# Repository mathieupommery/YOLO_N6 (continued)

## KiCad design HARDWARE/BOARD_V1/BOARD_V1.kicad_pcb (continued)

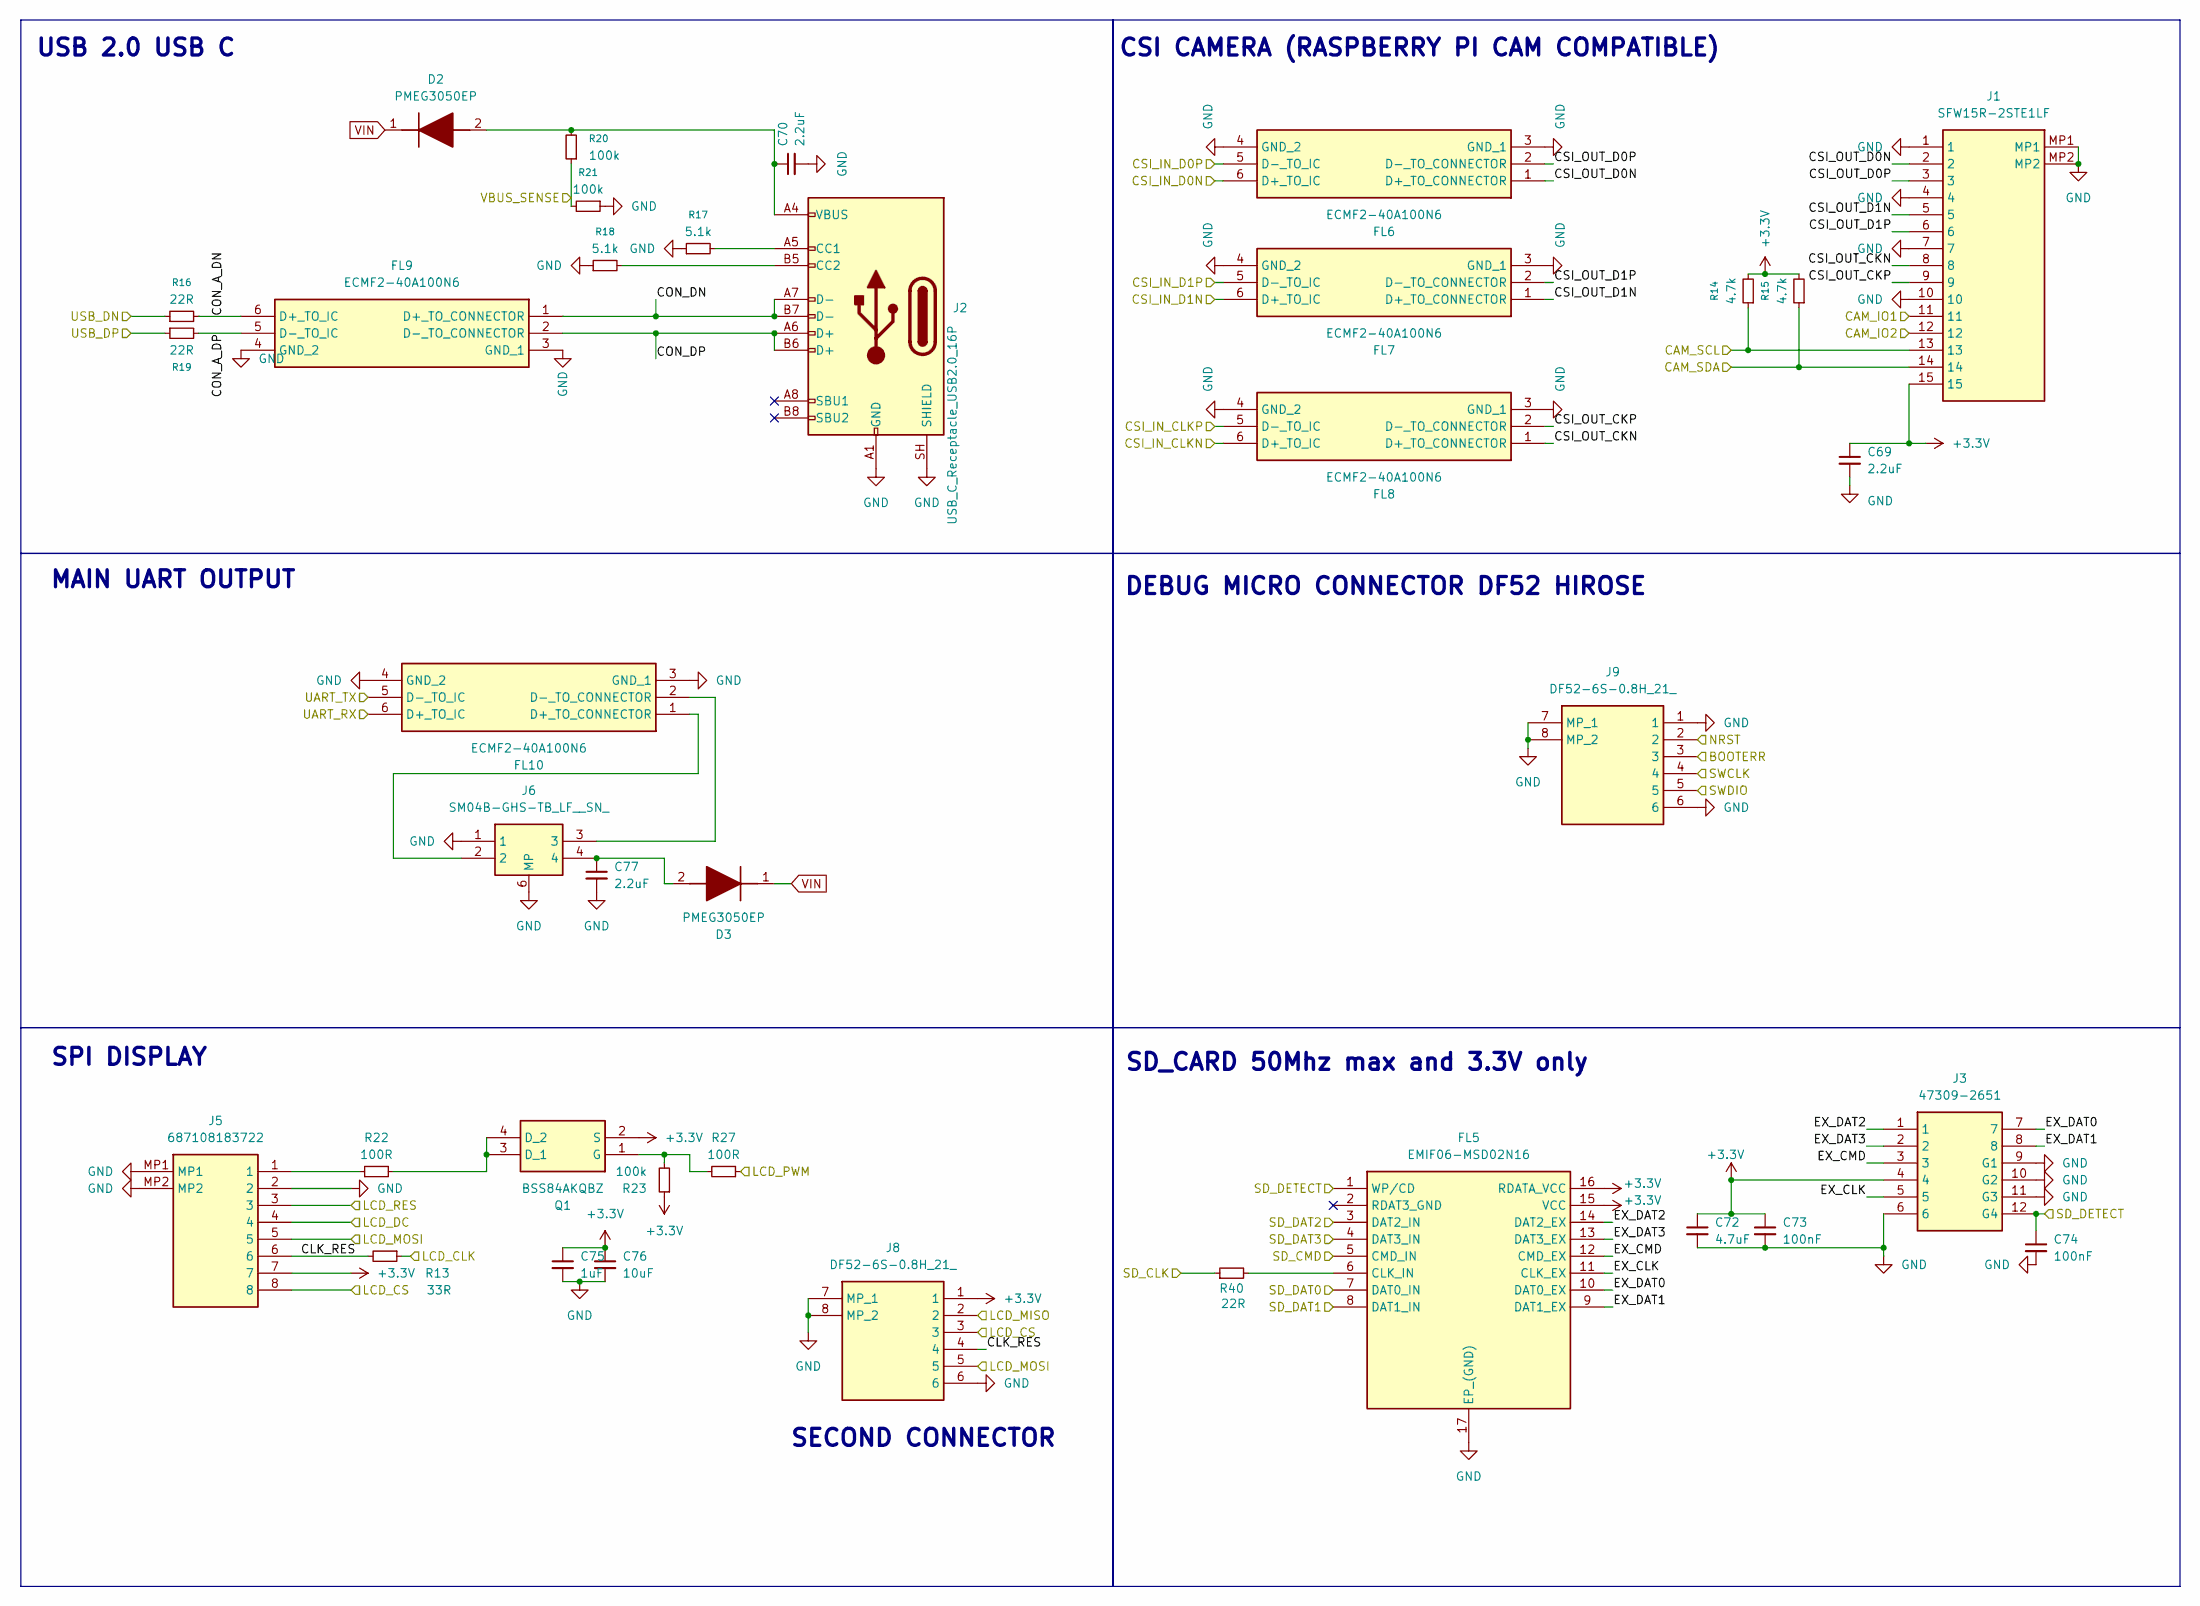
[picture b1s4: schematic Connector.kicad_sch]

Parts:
C69, C70, C77: 2.2uF; C_0402_1005Metric_Pad0.74x0.62mm_HandSolder
C72: 4.7uF; C_0402_1005Metric_Pad0.74x0.62mm_HandSolder
C73, C74: 100nF; C_0201_0603Metric_Pad0.64x0.40mm_HandSolder
C75: 1uF; C_0201_0603Metric_Pad0.64x0.40mm_HandSolder
C76: 10uF; C_0402_1005Metric_Pad0.74x0.62mm_HandSolder
D2, D3: PMEG3050EP; SOD4725X110N; Manufacturer_Part_Number PMEG3050EP; Mouser Part Number 771-PMEG3050EP115
FL5: EMIF06-MSD02N16; EMIF06MSD02N16; Manufacturer_Part_Number EMIF06-MSD02N16; Mouser Part Number 511-EMIF06-MSD02N16
FL6, FL7, FL8, FL9, FL10: ECMF2-40A100N6; ECMF240A100N6; Manufacturer_Part_Number ECMF2-40A100N6; Mouser Part Number 511-ECMF2-40A100N6
J1: SFW15R-2STE1LF; SFW15R2STE1LF; Manufacturer_Part_Number SFW15R-2STE1LF; Mouser Part Number 649-SFW15R-2STE1LF
J2: USB_C_Receptacle_USB2.0_16P; USB_C_Receptacle_GCT_USB4110; Mouser Part Number 640-USB4110-GF-A
J3: 47309-2651; 473092651; Manufacturer_Part_Number 47309-2651; Mouser Part Number 538-47309-2651
J5: 687108183722; Mouser Part Number 710-687108183722
J6: SM04B-GHS-TB_LF__SN_; SM04B-GHS-TB; Manufacturer_Part_Number SM04B-GHS-TB(LF)(SN); Mouser Part Number 306-SM04BGHSTBLFSN
J8, J9: DF52-6S-0.8H_21_; DF526S08H21; Manufacturer_Part_Number DF52-6S-0.8H(21); Mouser Part Number 798-DF52-6S-0.8H21
Q1: BSS84AKQBZ; 2N7002KQBZ; Mouser Part Number 771-2N7002KQBZ
R13: 33R; R_0201_0603Metric_Pad0.64x0.40mm_HandSolder
R14, R15: 4.7k; R_0201_0603Metric_Pad0.64x0.40mm_HandSolder
R16, R19, R40: 22R; R_0201_0603Metric_Pad0.64x0.40mm_HandSolder
R17, R18: 5.1k; R_0201_0603Metric_Pad0.64x0.40mm_HandSolder
R20, R21, R23: 100k; R_0201_0603Metric_Pad0.64x0.40mm_HandSolder
R22, R27: 100R; R_0201_0603Metric_Pad0.64x0.40mm_HandSolder

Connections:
+3.3V: C69.1, C72.1, C73.1, C75.1, C76.1, FL5.15 (VCC), FL5.16 (RDATA_VCC), J1.15, J3.4, J5.7, J8.1, Q1.2 (S), R14.2, R15.2, R23.1; also elsewhere on the board
/BOOT_ERROR: J9.3; also elsewhere on the board
/CAM_IO1: J1.11; also elsewhere on the board
/CAM_IO2: J1.12; also elsewhere on the board
/CAM_SCL: J1.13, R14.1; also elsewhere on the board
/CAM_SDA: J1.14, R15.1; also elsewhere on the board
/CSI_CKN: FL8.6 (D+_TO_IC); also elsewhere on the board
/CSI_CKP: FL8.5 (D-_TO_IC); also elsewhere on the board
/CSI_D0N: FL6.6 (D+_TO_IC); also elsewhere on the board
/CSI_D0P: FL6.5 (D-_TO_IC); also elsewhere on the board
/CSI_D1N: FL7.6 (D+_TO_IC); also elsewhere on the board
/CSI_D1P: FL7.5 (D-_TO_IC); also elsewhere on the board
/Connector/CLK_RES: J5.6, J8.4, R13.2
/Connector/CON_A_DN: FL9.6 (D+_TO_IC), R16.2
/Connector/CON_A_DP: FL9.5 (D-_TO_IC), R19.2
/Connector/CON_DN: FL9.1 (D+_TO_CONNECTOR), J2.A7 (D-), J2.B7 (D-)
/Connector/CON_DP: FL9.2 (D-_TO_CONNECTOR), J2.A6 (D+), J2.B6 (D+)
/Connector/CSI_OUT_CKN: FL8.1 (D+_TO_CONNECTOR), J1.8
/Connector/CSI_OUT_CKP: FL8.2 (D-_TO_CONNECTOR), J1.9
/Connector/CSI_OUT_D0N: FL6.1 (D+_TO_CONNECTOR), J1.2
/Connector/CSI_OUT_D0P: FL6.2 (D-_TO_CONNECTOR), J1.3
/Connector/CSI_OUT_D1N: FL7.1 (D+_TO_CONNECTOR), J1.5
/Connector/CSI_OUT_D1P: FL7.2 (D-_TO_CONNECTOR), J1.6
/Connector/EX_CLK: FL5.11 (CLK_EX), J3.5
/Connector/EX_CMD: FL5.12 (CMD_EX), J3.3
/Connector/EX_DAT0: FL5.10 (DAT0_EX), J3.7
/Connector/EX_DAT1: FL5.9 (DAT1_EX), J3.8
/Connector/EX_DAT2: FL5.14 (DAT2_EX), J3.1
/Connector/EX_DAT3: FL5.13 (DAT3_EX), J3.2
/LCD_CLK: R13.1; also elsewhere on the board
/LCD_CS: J5.8, J8.3; also elsewhere on the board
/LCD_DC: J5.4; also elsewhere on the board
/LCD_MISO: J8.2; also elsewhere on the board
/LCD_MOSI: J5.5, J8.5; also elsewhere on the board
/LCD_PWM: R27.1; also elsewhere on the board
/LCD_RES: J5.3; also elsewhere on the board
/NRST: J9.2; also elsewhere on the board
/SD_CLK: R40.1; also elsewhere on the board
/SD_CMD: FL5.5 (CMD_IN); also elsewhere on the board
/SD_DAT0: FL5.7 (DAT0_IN); also elsewhere on the board
/SD_DAT1: FL5.8 (DAT1_IN); also elsewhere on the board
/SD_DAT2: FL5.3 (DAT2_IN); also elsewhere on the board
/SD_DAT3: FL5.4 (DAT3_IN); also elsewhere on the board
/SD_DETECT: C74.1, FL5.1 (WP/CD), J3.12 (G4); also elsewhere on the board
/SWCLK: J9.4; also elsewhere on the board
/SWDIO: J9.5; also elsewhere on the board
/USART6_RX: FL10.6 (D+_TO_IC); also elsewhere on the board
/USART6_TX: FL10.5 (D-_TO_IC); also elsewhere on the board
/USB1_DN: R16.1; also elsewhere on the board
/USB1_DP: R19.1; also elsewhere on the board
/USB_VBUS_SENSE: R20.1, R21.2; also elsewhere on the board
GND: C69.2, C70.2, C72.2, C73.2, C74.2, C75.2, C76.2, C77.2, FL5.17 (EP_(GND)), FL6.3 (GND_1), FL6.4 (GND_2), FL7.3 (GND_1), FL7.4 (GND_2), FL8.3 (GND_1), FL8.4 (GND_2), FL9.3 (GND_1), FL9.4 (GND_2), FL10.3 (GND_1), FL10.4 (GND_2), J1.1, J1.4, J1.7, J1.10, J1.MP1, J1.MP2, J2.A1 (GND), J2.A12 (GND), J2.B1 (GND), J2.B12 (GND), J2.SH (SHIELD), J3.6, J3.9 (G1), J3.10 (G2), J3.11 (G3), J5.2, J5.MP1, J5.MP2, J6.1, J6.5 (MP), J6.6 (MP), J8.6, J8.7 (MP_1), J8.8 (MP_2), J9.1, J9.6, J9.7 (MP_1), J9.8 (MP_2), R17.1, R18.1, R21.1; also elsewhere on the board
unnamed: C70.1, D2.2 (A), J2.A4 (VBUS), J2.A9 (VBUS), J2.B4 (VBUS), J2.B9 (VBUS), R20.2
unnamed: C77.1, D3.2 (A), J6.4
unnamed: FL5.6 (CLK_IN), R40.2
unnamed: FL10.1 (D+_TO_CONNECTOR), J6.2
unnamed: FL10.2 (D-_TO_CONNECTOR), J6.3
unnamed: J2.A5 (CC1), R17.2
unnamed: J2.B5 (CC2), R18.2
unnamed: J5.1, R22.1
unnamed: Q1.3 (D_1), Q1.4 (D_2), R22.2
unnamed: Q1.1 (G), R23.2, R27.2
VIN: D2.1 (K), D3.1 (K); also elsewhere on the board

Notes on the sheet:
MAIN UART OUTPUT
USB 2.0 USB C
SD_CARD 50Mhz max and 3.3V only
DEBUG MICRO CONNECTOR DF52 HIROSE
CSI CAMERA (RASPBERRY PI CAM COMPATIBLE)
SECOND CONNECTOR
SPI DISPLAY

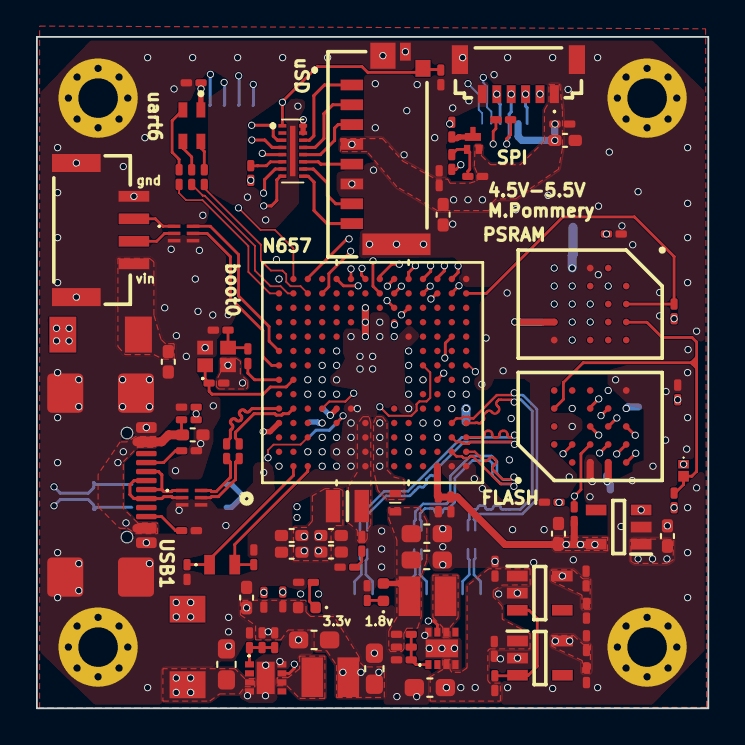
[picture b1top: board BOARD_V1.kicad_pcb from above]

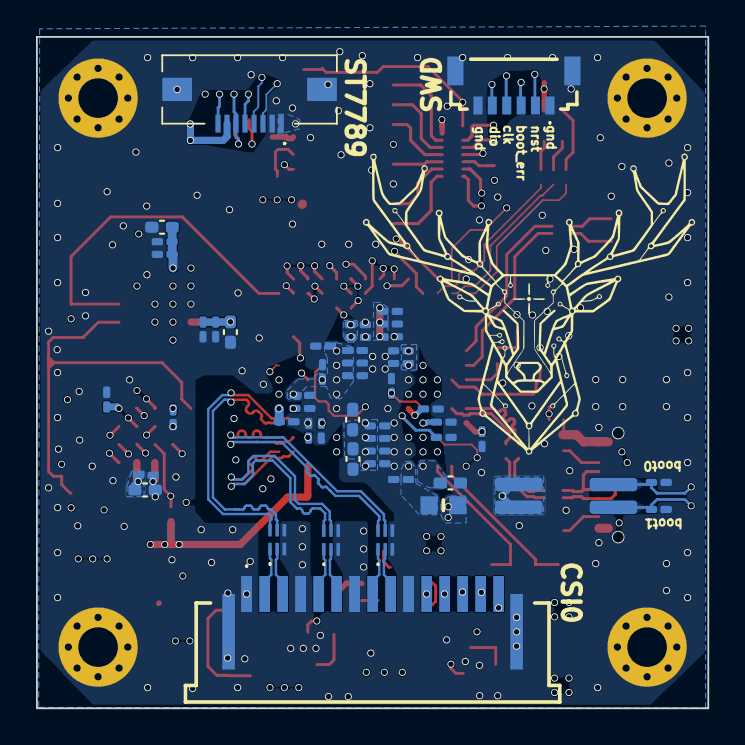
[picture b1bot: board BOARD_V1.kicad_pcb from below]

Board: 8 copper layers, 37.3 x 37.3 mm, 149 parts (50 on the bottom side), 109 nets.

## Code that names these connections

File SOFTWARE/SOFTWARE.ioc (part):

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Mcu.Name=STM32N657I0HxQ
Mcu.Package=VFBGA178
Mcu.UserName=STM32N657I0HxQ
PA13(JTMS/SWDIO).GPIOParameters=PinAttribute
PA13(JTMS/SWDIO).Mode=Trace_Asynchronous_SW
PA13(JTMS/SWDIO).PinAttribute=FSBL,AppliSecure,AppliNonSecure,ExtMemLoader
PA13(JTMS/SWDIO).Signal=DEBUG_JTMS-SWDIO
PA14(JTCK/SWCLK).GPIOParameters=PinAttribute
PA14(JTCK/SWCLK).Mode=Trace_Asynchronous_SW
PA14(JTCK/SWCLK).PinAttribute=FSBL,AppliSecure,AppliNonSecure,ExtMemLoader
PA14(JTCK/SWCLK).Signal=DEBUG_JTCK-SWCLK
PA6.Signal=BOOT1
PB5(JTDO/TRACESWO).GPIOParameters=PinAttribute
PB5(JTDO/TRACESWO).Mode=Trace_Asynchronous_SW
PB5(JTDO/TRACESWO).PinAttribute=FSBL,AppliSecure,AppliNonSecure,ExtMemLoader
PB5(JTDO/TRACESWO).Signal=DEBUG_JTDO-SWO
PD3.ContextOwner=FSBL
PD3.GPIOParameters=GPIO_Label,PinAttribute
PD3.GPIO_Label=BLUE
PD3.PinAttribute=FSBL
PD3.Signal=GPIO_Output
PD4.ContextOwner=FSBL
PD4.GPIOParameters=GPIO_Label,PinAttribute
PD4.GPIO_Label=GREEN
PD4.PinAttribute=FSBL
PD4.Signal=GPIO_Output
PE8.ContextOwner=FSBL
PE8.GPIOParameters=GPIO_Label,PinAttribute
PE8.GPIO_Label=RED
PE8.PinAttribute=FSBL
PE8.Signal=GPIO_Output
PH0-OSC_IN(PH0).GPIOParameters=PinAttribute
PH0-OSC_IN(PH0).Mode=HSE-External-Oscillator
PH0-OSC_IN(PH0).PinAttribute=Free
PH0-OSC_IN(PH0).Signal=RCC_OSC_IN
PH1-OSC_OUT(PH1).GPIOParameters=PinAttribute
PH1-OSC_OUT(PH1).Mode=HSE-External-Oscillator
PH1-OSC_OUT(PH1).PinAttribute=Free
PH1-OSC_OUT(PH1).Signal=RCC_OSC_OUT
RCC.HSE_VALUE=48000000
board=custom
